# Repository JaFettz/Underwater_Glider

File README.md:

# Underwater_Glider
Code for my College project

Prototype:

Circuit:

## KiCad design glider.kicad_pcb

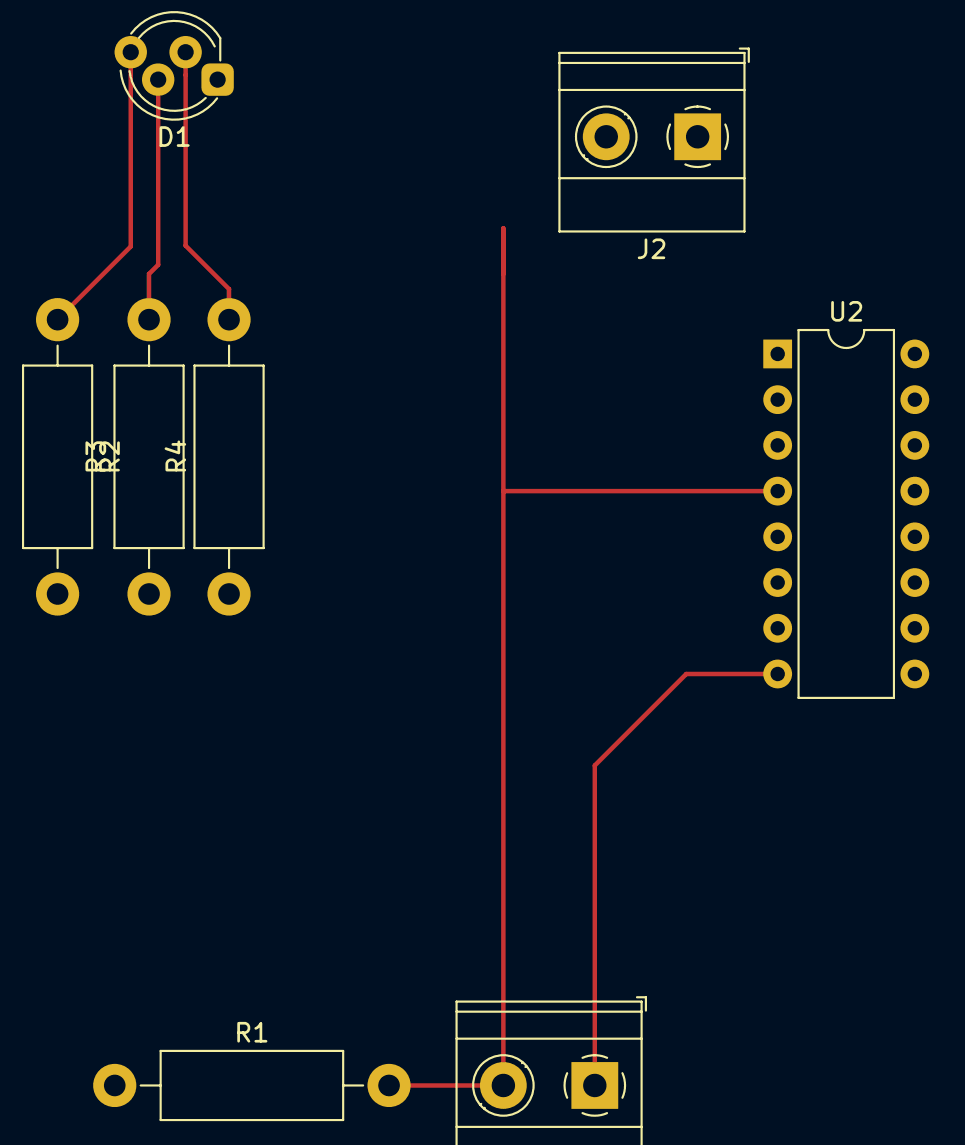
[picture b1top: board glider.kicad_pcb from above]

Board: 2 copper layers, 8 parts (0 on the bottom side), 8 nets.

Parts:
D1: LED_ARGB; LED_D5.0mm-4_RGB_Staggered_Pins
J1: Conn_01x02_Male; TerminalBlock_Phoenix_MKDS-1,5-2-5.08_1x02_P5.08mm_Horizont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
J2: Conn_01x02_Female; TerminalBlock_Phoenix_MKDS-1,5-2-5.08_1x02_P5.08mm_Horizont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
R1, R2, R3, R4: R; R_Axial_DIN0411_L9.9mm_D3.6mm_P15.24mm_Horizontal
U2: L293D; DIP-16_W7.62mm

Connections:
unnamed: D1.2, R4.2
unnamed: D1.3, R3.2
unnamed: D1.4, R2.1
unnamed: J1.1, U2.8
unnamed: J1.2, R1.2, U2.4, U2.5
unnamed: J2.1, U2.3
unnamed: J2.2, U2.6
unnamed: U2.1, U2.2, U2.7, U2.16

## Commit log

2019-03-23 Add files via upload
    Diseño inicial del proyecto
2019-04-29 Segunda versión del codigo
2019-04-30 Update Glider.ino
    se agrego el blink del en la estado de espera.
2019-04-30 Update Glider.ino
    iman ahora activa el switch
2019-04-30 Update Glider.ino
    ajustes en el codigo
2020-06-29 circuit design files
